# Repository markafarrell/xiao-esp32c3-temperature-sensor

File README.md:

### Requirements

* [esptool](https://pypi.org/project/esptool/)
* [micropython]( https://micropython.org/download/esp32c3/)
* [mpremote](https://github.com/dhylands/rshell)

## Flash Firmware

1. Install esptool

```
pip install esptool
```

2. Get circuitpython

```
mkdir -p micropython
cd micropython
curl -O https://micropython.org/resources/firmware/ESP32_GENERIC_C3-20230426-v1.20.0.bin
```

3. Start ESP32C3 in bootloader mode (hold down boot button while powering up)

4. Identify serial device

```
sudo dmesg | grep "USB ACM device" | tail -1
```

```
[24659.642354] cdc_acm 1-1:1.0: ttyACM0: USB ACM device
```

5. Erase flash

```
esptool.py --chip esp32c3 --port /dev/ttyACM0 erase_flash
```

6. Flash circuit python firmware

```
esptool.py --chip esp32c3 --port /dev/ttyACM0 --baud 460800 write_flash -z 0x0 micropython/ESP32_GENERIC_C3-20230426-v1.20.0.bin
```

### Install

1. Install requests

```
mpremote a0 mip install requests
```

2. Install application

```
mpremote a0 cp src/secrets.py :secrets.py
mpremote a0 cp src/sensor_mapping.py :sensor_mapping.py
mpremote a0 cp src/main.py :main.py
```

3. Run application

```
mpremote a0 run src/main.py
```

## Monitor Serial

### Connect

```
mpremote a0
```

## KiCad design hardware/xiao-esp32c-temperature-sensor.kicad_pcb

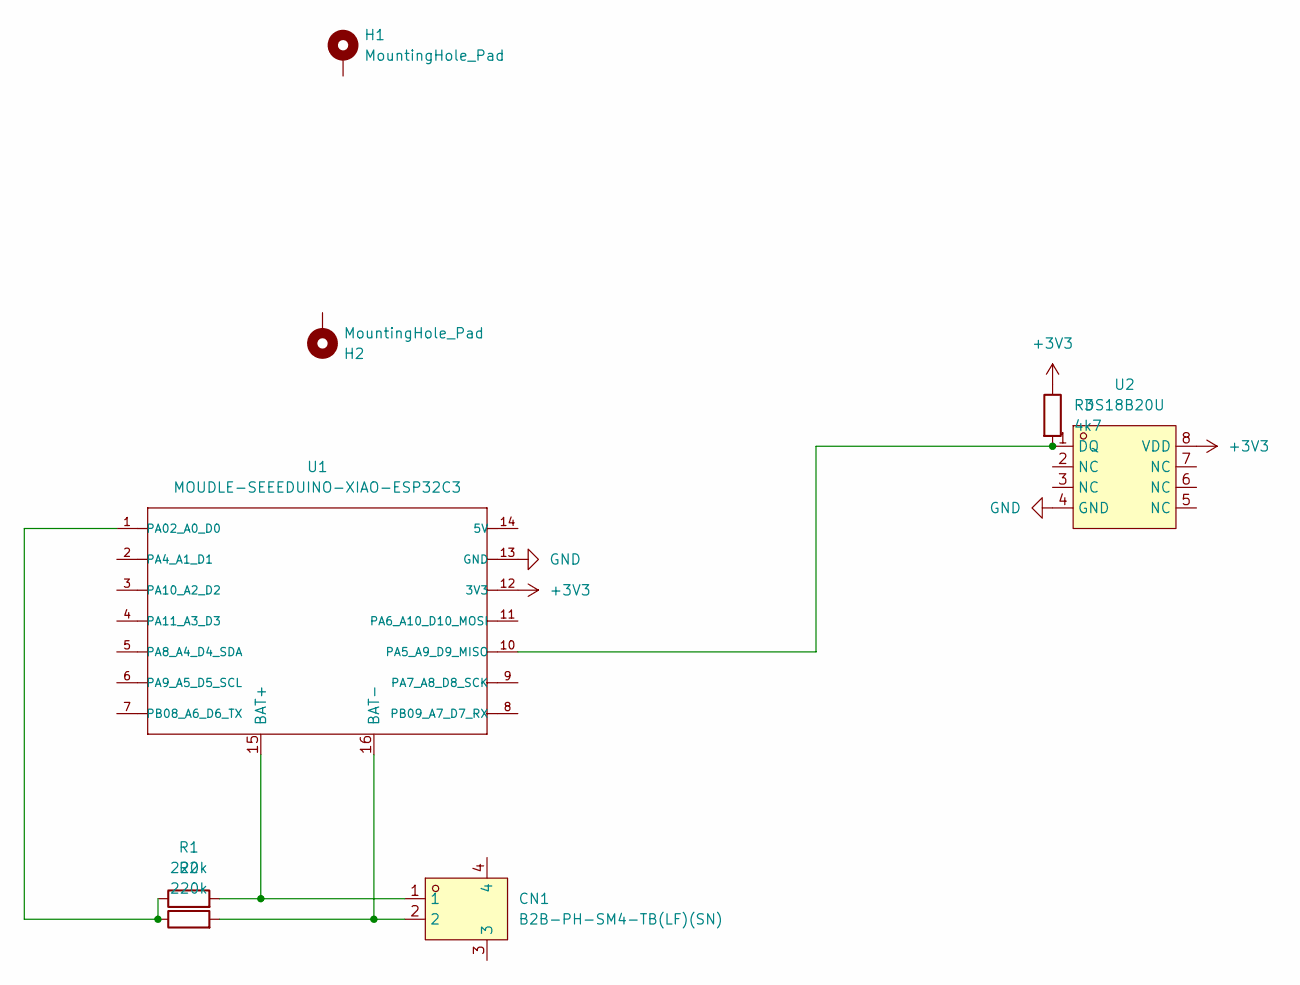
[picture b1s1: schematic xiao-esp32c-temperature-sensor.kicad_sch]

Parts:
CN1: B2B-PH-SM4-TB(LF)(SN); CONN-SMD_B2B-PH-SM4-TB-LF-SN; LCSC Part C160352
H1, H2: MountingHole_Pad; MountingHole_2.2mm_M2_DIN965_Pad
R1, R2: 220k; R_0805_2012Metric_Pad1.20x1.40mm_HandSolder
R3: 4k7; R_0805_2012Metric_Pad1.20x1.40mm_HandSolder
U1: MOUDLE-SEEEDUINO-XIAO-ESP32C3; MOUDLE14P-SMD-2.54-21X17.8MM-bat
U2: DS18B20U; MSOP-8_L3.0-W3.0-P0.65-LS4.9-BL; LCSC Part C695836

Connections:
+3V3: R3.1, U1.12 (3V3), U2.8 (VDD)
GND: U1.13 (GND), U2.4 (GND)
unnamed: CN1.1, R1.2, U1.15 (BAT+)
unnamed: CN1.2, R2.2, U1.16 (BAT-)
unnamed: R1.1, R2.1, U1.1 (PA02_A0_D0)
unnamed: R3.2, U1.10 (PA5_A9_D9_MISO), U2.1 (DQ)

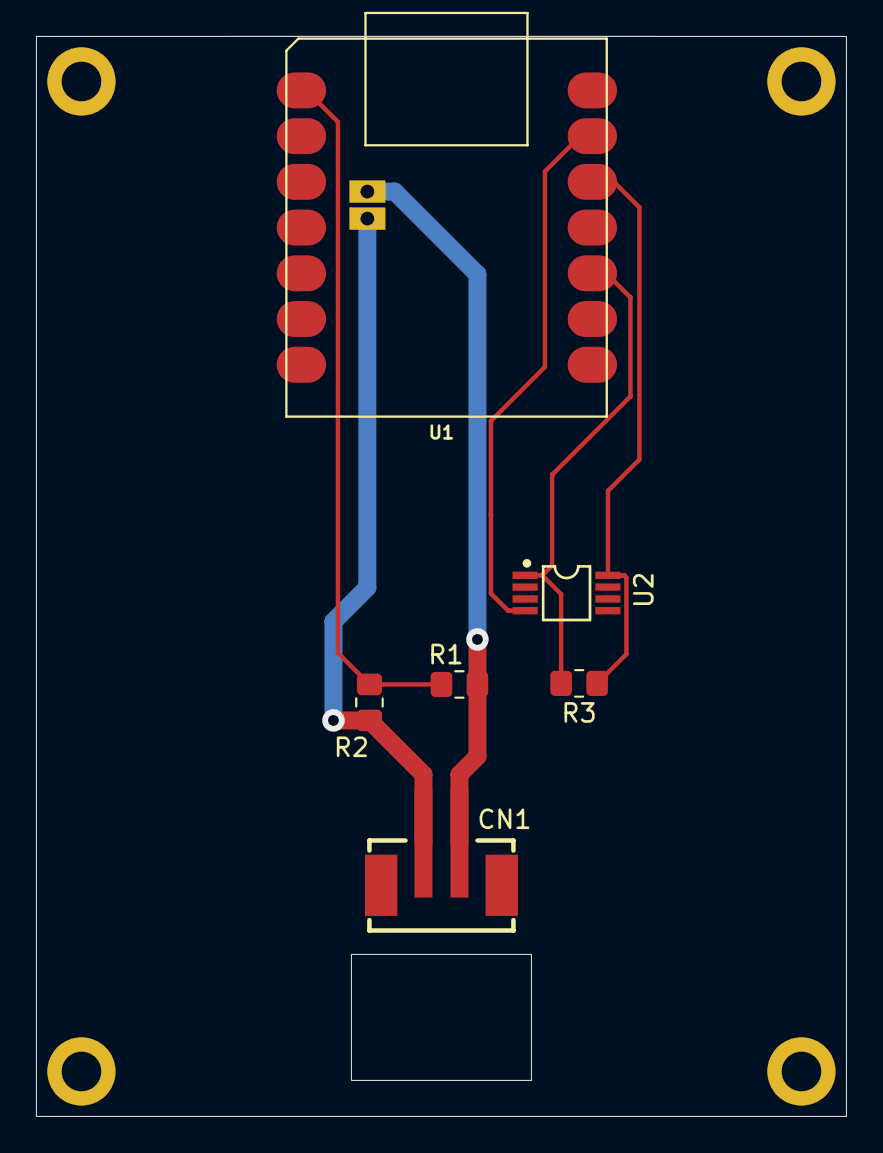
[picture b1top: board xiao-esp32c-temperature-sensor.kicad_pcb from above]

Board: 2 copper layers, 45.0 x 60.0 mm, 10 parts (0 on the bottom side), 6 nets.

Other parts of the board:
H3, H4: MountingHole_Pad; MountingHole_2.2mm_M2_DIN965_Pad

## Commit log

2023-09-13 web config stuff
2023-11-25 fixes
